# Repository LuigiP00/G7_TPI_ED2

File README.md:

# G7_TPI_ED2 — Pulsómetro digital con alarma térmica

Trabajo Práctico Integrador de **Electrónica Digital 2** (FCEFyN – UNC), Grupo 7.

Sistema basado en el **PIC16F887** (cristal de 4 MHz, Assembler MPASM) que mide la frecuencia cardíaca con un sensor óptico de pulso y la temperatura con un LM35. Muestra los valores en un display de 7 segmentos de 4 dígitos, los envía a una GUI en la PC por la EUSART y activa una alarma (buzzer y LED rojo) cuando la temperatura supera los 40 °C.

**Integrantes:** Echenique, Matías · Marquez, Lionel · Pandolfi, Luigi Nicola · Rodríguez, Octavio
**Profesor:** Ing. Emiliano Migliore · **Comisión:** 4.1

## Estructura del repositorio

| Carpeta | Contenido |
| --- | --- |
| `anteproyecto/` | Anteproyecto entregado (`G7_AP_TPI_ED2`) y diagramas de bloques en draw.io |
| `informe/` | Borrador del informe final |
| `hardware/kicad/` | Esquemático y PCB en KiCad (`G7_Placa_TPI.kicad_pro`) |
| `hardware/datasheets/` | Hojas de datos de los componentes |
| `firmware/` | Código Assembler del SEP (`G7_TPI_ED2.asm`, v4.0) |
| `firmware/pruebas/` | Programas de prueba de la placa y versiones anteriores |
| `gui/` | Interfaz gráfica web para la PC (`index.html`, Web Serial) |
| `docs/` | Protocolo serie y diagrama de bloques del SEP para el informe (`docs/diagramas/`) |

## Firmware: cómo compilar y cargar

1. En MPLAB X: *File → New Project → Standalone Project*, dispositivo **PIC16F887**, ensamblador **mpasm**.
2. Agregar `firmware/G7_TPI_ED2.asm` al proyecto y compilar (*Build*).
3. Cargar el `.hex` generado con **AN1310** a través del adaptador USB–UART (el PIC ya tiene el bootloader).

Los `.asm` están codificados en **Windows-1252**, igual que la plantilla de la cátedra, para que los acentos se vean bien en MPLAB X.

## Asignación de pines (placa actual)

| Pin | Señal |
| --- | --- |
| RA0 / AN0 | LM35 |
| RA1 / AN1 | Sensor de pulso HW-827 (divisor 22 kΩ / 22 kΩ) |
| RA3 / VREF+ | Referencia del ADC: 2,50 V |
| RB6 | LED verde (temperatura normal) |
| RB7 | LED rojo (alarma térmica) |
| RC0–RC3 | Dígitos del display (PNP BC557, ánodo común) |
| RC4 | Buzzer (vía BC337) |
| RD0–RD6 | Segmentos a–g |
| RC6 / RC7 | TX / RX hacia el CP2102 |

La medición de pulso se inicia desde la PC (tecla `I` en la GUI); la placa no tiene botón de inicio.

## Protocolo serie

9600 bps, 8N1. Detalle en [`docs/protocolo_serie.md`](docs/protocolo_serie.md).

## Estado

| Parte | Estado |
| --- | --- |
| Anteproyecto | Aprobado (diagrama de bloques rehecho con el formato de la cátedra en `docs/diagramas/`) |
| Placa | Fabricada y probada |
| Firmware v4.0: temperatura con alarma, conteo de pulso de 15 s, display, EUSART | Funcionando en la placa |
| GUI web | Funcionando |
| Calibración del pulso contra una referencia (oxímetro o conteo manual) | Pendiente |
| Informe final | En redacción (`informe/`) |

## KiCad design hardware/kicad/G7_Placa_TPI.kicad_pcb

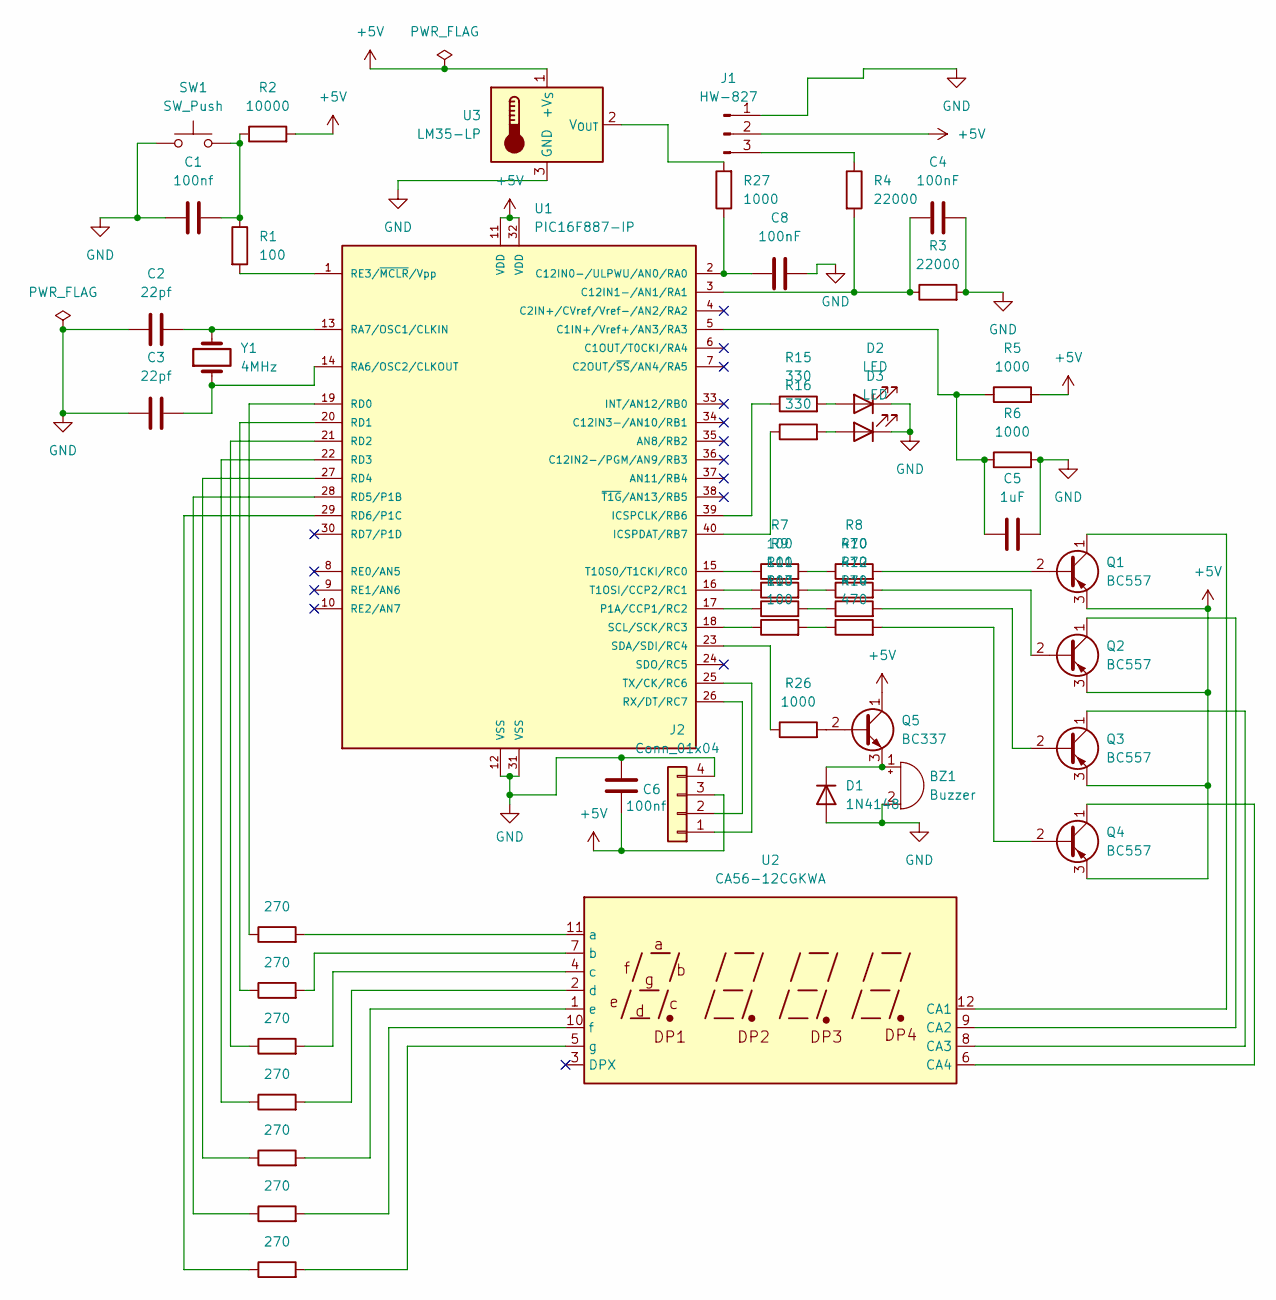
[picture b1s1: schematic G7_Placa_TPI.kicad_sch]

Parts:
BZ1: Buzzer; Buzzer_12x9.5RM7.6
C1, C6: 100nf; C_Disc_D5.0mm_W2.5mm_P5.00mm
C2, C3: 22pf; C_Disc_D5.0mm_W2.5mm_P5.00mm
C4, C8: 100nF; C_Disc_D5.0mm_W2.5mm_P5.00mm
C5: 1uF; C_Disc_D5.0mm_W2.5mm_P5.00mm
D1: 1N4148; D_DO-35_SOD27_P7.62mm_Horizontal
D2, D3: LED; LED_D5.0mm
J1: HW-827; PinHeader_1x03_P2.54mm_Vertical
J2: Conn_01x04; PinHeader_1x04_P2.54mm_Vertical
Q1, Q2, Q3, Q4: BC557; TO-92_Inline
Q5: BC337; TO-92_Inline
R1, R7, R9, R11, R13: 100; R_Axial_DIN0207_L6.3mm_D2.5mm_P7.62mm_Horizontal
R2: 10000; R_Axial_DIN0207_L6.3mm_D2.5mm_P7.62mm_Horizontal
R3, R4: 22000; R_Axial_DIN0207_L6.3mm_D2.5mm_P7.62mm_Horizontal
R5, R6, R26, R27: 1000; R_Axial_DIN0207_L6.3mm_D2.5mm_P7.62mm_Horizontal
R8, R10, R12, R14: 470; R_Axial_DIN0207_L6.3mm_D2.5mm_P7.62mm_Horizontal
R15, R16: 330; R_Axial_DIN0207_L6.3mm_D2.5mm_P7.62mm_Horizontal
R19, R20, R21, R22, R23, R24, R25: 270; R_Axial_DIN0207_L6.3mm_D2.5mm_P7.62mm_Horizontal
SW1: SW_Push; PinHeader_1x02_P2.54mm_Vertical
U1: PIC16F887-IP; DIP-40_W15.24mm
U2: CA56-12CGKWA
U3: LM35-LP; TO-92_Inline
Y1: 4MHz; Crystal_HC49-U_Vertical

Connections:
+5V: C6.2, J1.2, J2.3, Q1.3 (E), Q2.3 (E), Q3.3 (E), Q4.3 (E), Q5.1 (C), R2.2, R5.2, U1.11 (VDD), U1.32 (VDD), U3.1 (+V_{S})
GND: BZ1.2 (-), C1.2, C2.2, C3.2, C4.1, C5.1, C6.1, C8.1, D1.2 (A), D2.1 (K), D3.1 (K), J1.1, J2.4, R3.2, R6.2, SW1.1, U1.12 (VSS), U1.31 (VSS), U3.3 (GND)
unnamed: BZ1.1 (+), D1.1 (K), Q5.3 (E)
unnamed: C1.1, R1.1, R2.1, SW1.2
unnamed: D2.2 (A), R15.2
unnamed: D3.2 (A), R16.2
unnamed: J1.3, R4.1
unnamed: J2.1, U1.25 (TX/CK/RC6)
unnamed: J2.2, U1.26 (RX/DT/RC7)
unnamed: Q1.2 (B), R8.2
unnamed: Q1.1 (C), U2.12 (CA1)
unnamed: Q2.2 (B), R10.2
unnamed: Q2.1 (C), U2.9 (CA2)
unnamed: Q3.2 (B), R12.2
unnamed: Q3.1 (C), U2.8 (CA3)
unnamed: Q4.2 (B), R14.2
unnamed: Q4.1 (C), U2.6 (CA4)
unnamed: Q5.2 (B), R26.2
unnamed: R7.2, R8.1
unnamed: R9.2, R10.1
unnamed: R11.2, R12.1
unnamed: R13.2, R14.1
unnamed: C5.2, R5.1, R6.1, U1.5 (C1IN+/Vref+/AN3/RA3)
unnamed: C8.2, R27.1, U1.2 (C12IN0-/ULPWU/AN0/RA0)
unnamed: C4.2, R3.1, R4.2, U1.3 (C12IN1-/AN1/RA1)
unnamed: R15.1, U1.39 (ICSPCLK/RB6)
unnamed: R16.1, U1.40 (ICSPDAT/RB7)
unnamed: R11.1, U1.17 (P1A/CCP1/RC2)
unnamed: C3.1, U1.14 (RA6/OSC2/CLKOUT), Y1.1
unnamed: C2.1, U1.13 (RA7/OSC1/CLKIN), Y1.2
unnamed: R19.1, U1.19 (RD0)
unnamed: R20.1, U1.20 (RD1)
unnamed: R21.1, U1.21 (RD2)
unnamed: R22.1, U1.22 (RD3)
unnamed: R23.1, U1.27 (RD4)
unnamed: R24.1, U1.28 (RD5/P1B)
unnamed: R25.1, U1.29 (RD6/P1C)
unnamed: R1.2, U1.1 (RE3/~MCLR/Vpp)
unnamed: R13.1, U1.18 (SCL/SCK/RC3)
unnamed: R26.1, U1.23 (SDA/SDI/RC4)
unnamed: R9.1, U1.16 (T1OSI/CCP2/RC1)
unnamed: R7.1, U1.15 (T10S0/T1CKI/RC0)
unnamed: R19.2, U2.11 (a)
unnamed: R20.2, U2.7 (b)
unnamed: R21.2, U2.4 (c)
unnamed: R22.2, U2.2 (d)
unnamed: R23.2, U2.1 (e)
unnamed: R24.2, U2.10 (f)
unnamed: R25.2, U2.5 (g)
unnamed: R27.2, U3.2 (V_{OUT})

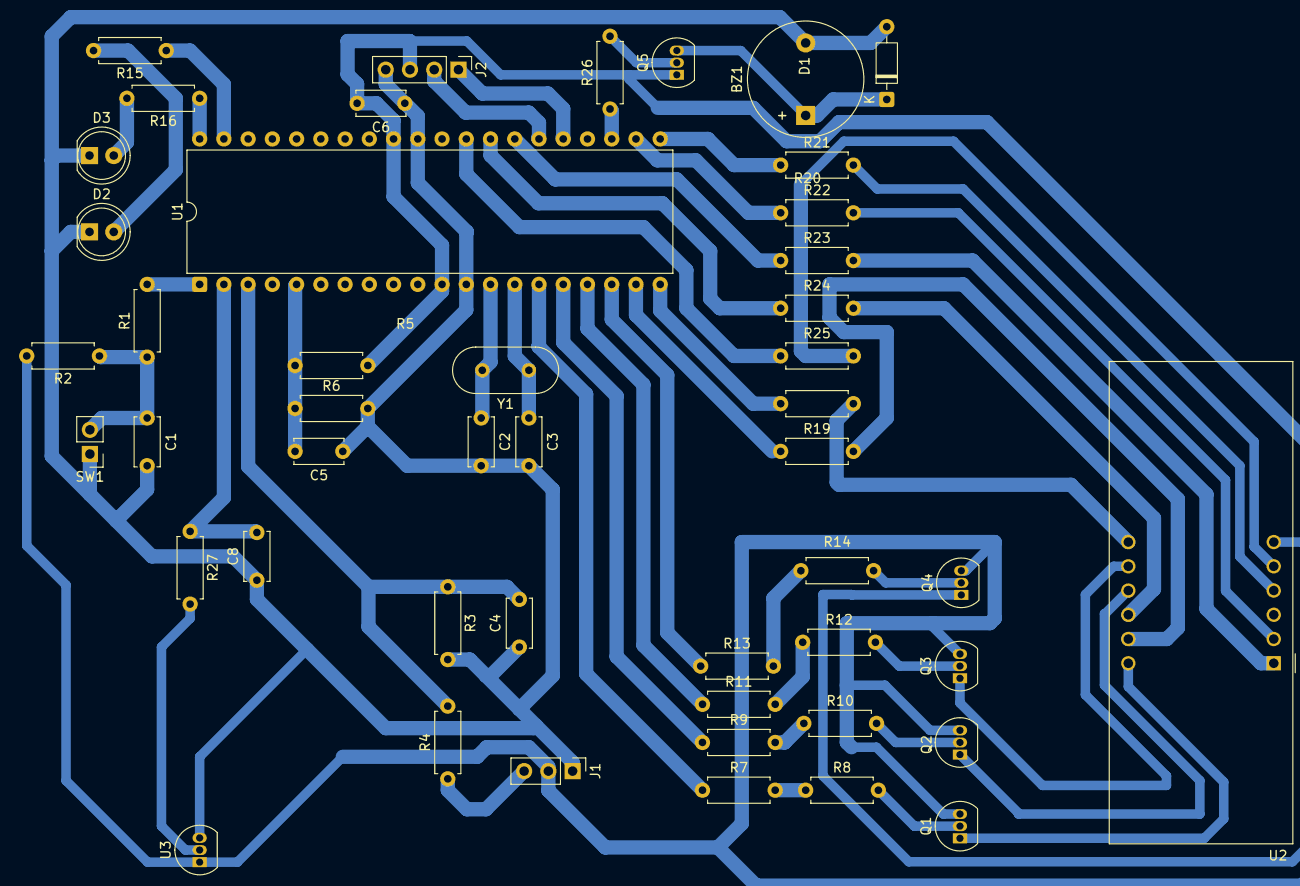
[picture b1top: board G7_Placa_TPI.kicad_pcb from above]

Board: 2 copper layers, 48 parts (0 on the bottom side), 50 nets.
